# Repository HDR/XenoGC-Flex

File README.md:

# A XenoGC clone that is easier to flash and install (Current revision is untested)

## Ordering

[With ISP Header](https://oshpark.com/shared_projects/uoXTTZRa)

[Without ISP Header](https://oshpark.com/shared_projects/8Vf3wffB)

Make sure you select Flex on checkout

## Flashing

Flashing is done over isp, a raspberry pi can be used for this, see https://github.com/HDR/RaspberryPi_ISP

```
sudo avrdude -p m8 -C ~/avrdude_gpio.conf -c pi_1 -U lfuse:w:0xe4:m -U hfuse:w:0xd9:m
sudo avrdude -p m8 -C ~/avrdude_gpio.conf -c pi_1 -U flash:w:XenoGC-Firmware.hex
```

## BOM

| Reference        | Part Number           | Description  |
| ------------- |:-------------:| -----:|
| R1 | 330Ω 0603 Resistor | LED Resistor |
| R2 | 330Ω 0603 Resistor | LED Resistor |
| R3 | 1KΩ 0603 Resistor | Reset Resistor |
| C1 | 100nF 0603 Capacitor |  |
| C2 | 100nF 0603 CapacitorV |  |
| U1 | Atmega8A-AU |  |

[Interactive BOM](http://MartinRefseth.com/ibom/XenoGC)

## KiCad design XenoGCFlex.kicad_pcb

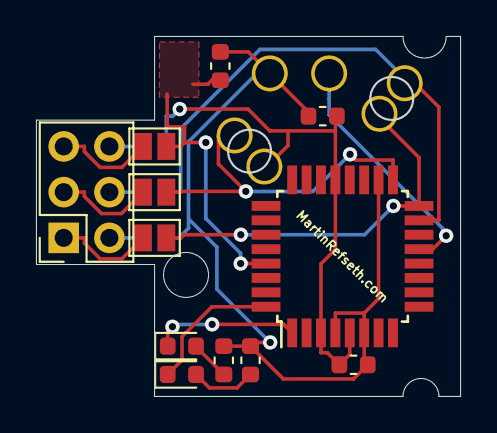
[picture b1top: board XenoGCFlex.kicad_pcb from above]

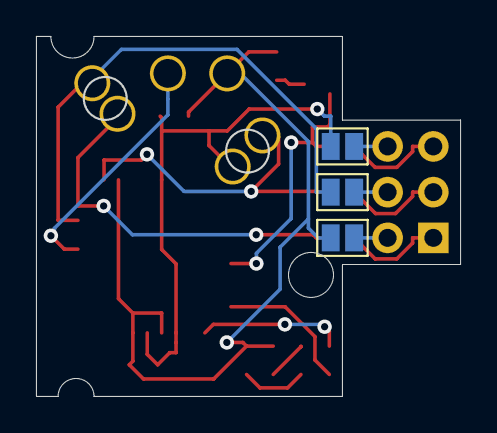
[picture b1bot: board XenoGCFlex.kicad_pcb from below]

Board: 2 copper layers, 23.5 x 19.9 mm, 21 parts (3 on the bottom side), 17 nets.

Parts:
C1, C2: 100nF; C_0603_1608Metric
D1: GRN; LED_0603_1608Metric
D2: RED; LED_0603_1608Metric
GC1: VCC; TestPoint_Plated_Hole_D1.6mm
GC5: PB1; TestPoint_Plated_Hole_D1.6mm
GC6: GND; TestPoint_Plated_Hole_D1.6mm
GC7: SCK; TestPoint_Plated_Hole_D1.6mm
GC8: MOSI; TestPoint_Plated_Hole_D1.6mm
GC9: MISO; TestPoint_Plated_Hole_D1.6mm
J1: AVR-ISP-6; PinSocket_2x03_P2.54mm_Vertical
JP1, JP2, JP3, JP4, JP5, JP6: Jumper; SolderJumper-2_P1.3mm_Open_Pad1.0x1.5mm
R1, R2: 330; R_0603_1608Metric
R3: 1K; R_0603_1608Metric
U1: ATmega8A-AU; TQFP-32_7x7mm_P0.8mm

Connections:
GND: C1.2, C2.1, GC6.1, JP6.2, U1.3, U1.5, U1.21
MISO: GC9.1, JP1.2, U1.16
MOSI: GC8.1, JP4.2, U1.15
unnamed: D1.1, U1.32
unnamed: D1.2, R1.2
unnamed: D2.1, U1.1
unnamed: D2.2, R2.2
unnamed: J1.1, JP1.1
unnamed: J1.2, JP2.1
unnamed: J1.3, JP3.1
unnamed: J1.4, JP4.1
unnamed: J1.5, JP5.1
unnamed: J1.6, JP6.1
PB1: GC5.1, U1.13
RESET: JP5.2, R3.2, U1.29
SCK: GC7.1, JP3.2, U1.17
VCC: C1.1, C2.2, GC1.1, JP2.2, R1.1, R2.1, R3.1, U1.4, U1.6, U1.18

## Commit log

2020-06-27 add some stuff
2020-06-28 Initial board revision
2020-06-28 Add Readme
2020-06-28 small visual update
2020-06-30 Add a version without isp headers, add some stuff to the silkscreen
2020-06-30 Remove text
2020-08-20 Add dumped firmawre and flashing instructions
